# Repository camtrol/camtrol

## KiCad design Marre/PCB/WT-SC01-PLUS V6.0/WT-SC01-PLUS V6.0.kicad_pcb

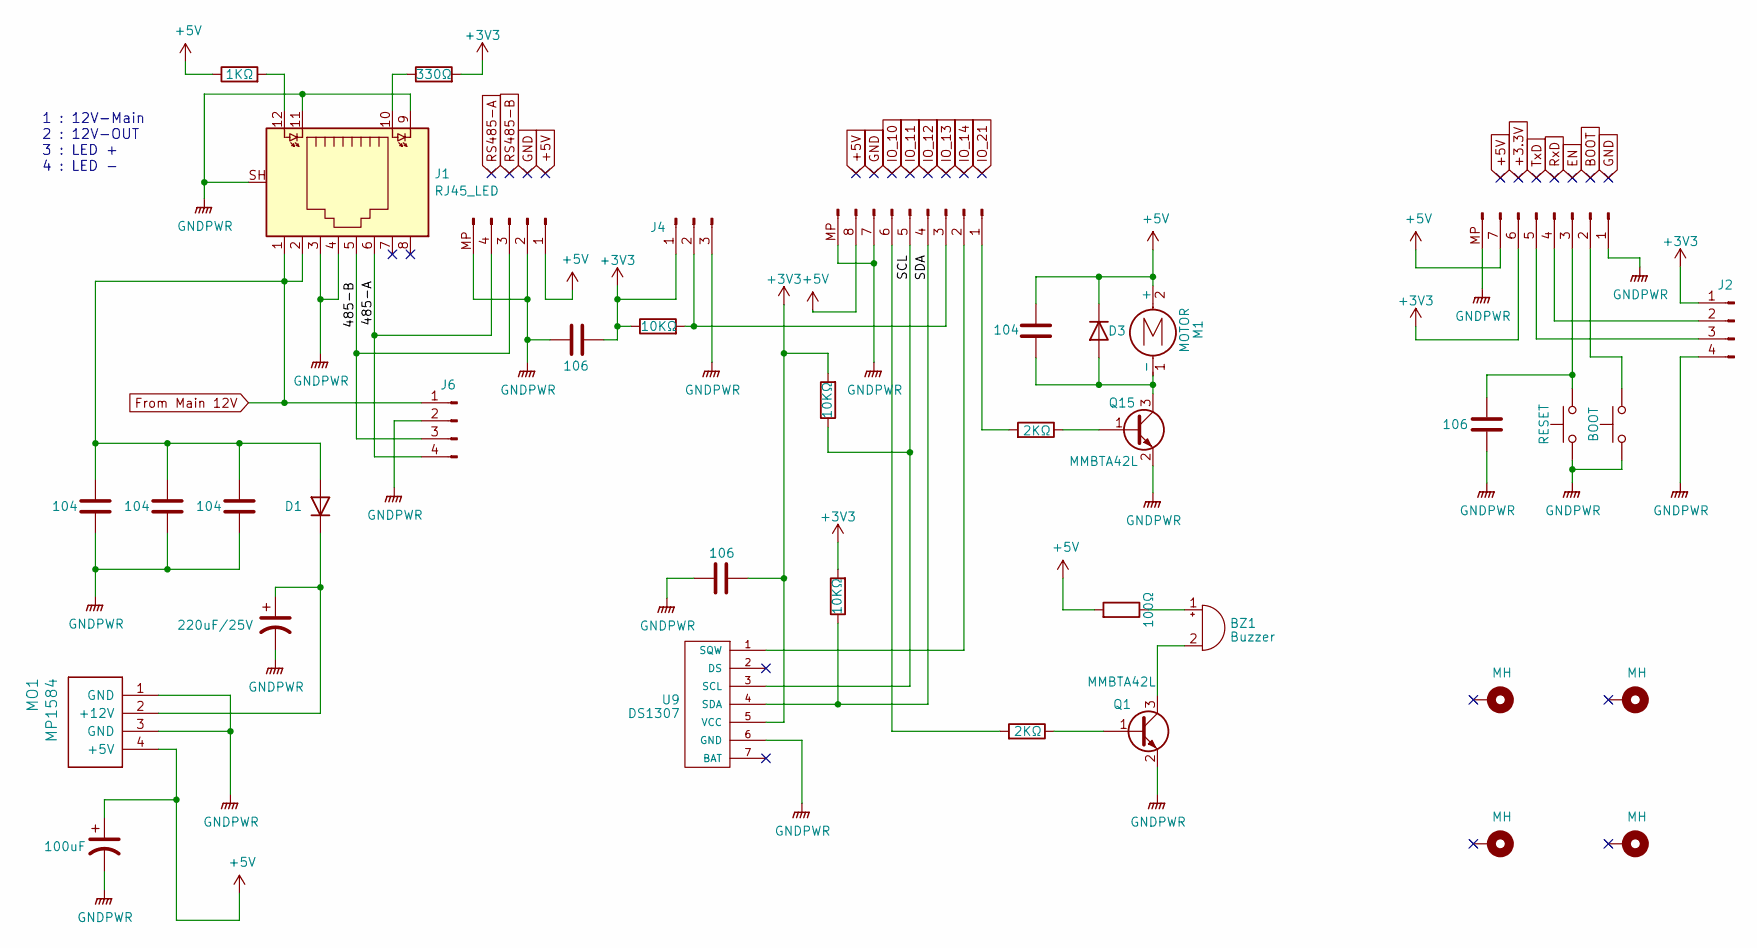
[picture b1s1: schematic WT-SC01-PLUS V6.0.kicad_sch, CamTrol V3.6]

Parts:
BZ1: Buzzer; Buzzer_12x9.5RM7.6
C1, C2, C5: 106; C_0805_HandSoldering
C3, C4, C15, C16: 104; C_0805_HandSoldering
C17: 100uF; CP_Elec_6.3x5.3
C22: 220uF/25V; CP_Radial_D8.0mm_P3.50mm
D1, D3: SS34; D_SMA
H3, H4, H5, H6: MH; MountingHole_SC01
J1: RJ45_LED; RJ45_LED_SMD
J2: 5267-04P; Molex_SPOX_5267-04A_1x04_P2.50mm_Vertical
J3: Conn_01x04_Pin; JST_GH_SM04B-GHS-TB_1x04-1MP_P1.25mm_Horizontal
J4: Conn_01x03_Pin; PhoenixContact_MCV_1,5_3-G-3.81_1x03_P3.81mm_Vertical
J5: Conn_01x08_Pin; JST_GH_SM08B-GHS-TB_1x08-1MP_P1.25mm_Horizontal
J6: 5267-04P; XH2.54-4P
J7: Conn_01x8_Male; JST_GH_SM07B-GHS-TB_1x07-1MP_P1.25mm_Horizontal
M1: MOTOR; 3610-Motor
MO1: MP1584; TZT-SMD
Q1, Q15: MMBTA42L; SOT-23
R1, R42, R43: 10KΩ; R_0805_HandSoldering
R2, R17: 2KΩ; R_0805_HandSoldering
R3: 100Ω; R_0805_HandSoldering
R4: 330Ω; R_0805_HandSoldering
R40: 1KΩ; R_0805_HandSoldering
SW1: BOOT; TS-3404
SW2: RESET; TS-3404
U9: DS1307

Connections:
+3V3: C1.1, C2.2, J2.1, J4.1, J7.6, R1.1, R4.2, R42.2, R43.2, U9.5 (VCC)
+5V: C3.1, C17.1, D3.2 (K), J3.1, J5.8, J7.7, M1.2 (+), MO1.4 (+5V), R3.2, R40.1
/485-A: J1.6, J3.4, J6.4
/485-B: J1.5, J3.3, J6.3
/SCL: J5.5, R42.1, U9.3 (SCL)
/SDA: J5.4, R43.1, U9.4 (SDA)
From Main 12V: C4.2, C15.2, C16.2, D1.1 (A), J1.1, J1.2, J6.1
GNDPWR: C1.2, C2.1, C4.1, C5.1, C15.1, C16.1, C17.2, C22.2, J1.3, J1.4, J1.9, J1.11, J1.SH, J2.4, J3.2, J3.MP (Pin_5), J4.3, J5.7, J5.MP (Pin_9), J6.2, J7.1, J7.MP (Pin_8), MO1.1 (GND), MO1.3 (GND), Q1.2 (E), Q15.2 (E), SW1.1, SW2.1, U9.6 (GND)
unnamed: BZ1.2 (+), Q1.3 (C)
unnamed: BZ1.1 (-), R3.1
unnamed: C22.1, D1.2 (K), MO1.2 (+12V)
unnamed: C3.2, D3.1 (A), M1.1 (-), Q15.3 (C)
unnamed: J1.10, R4.1
unnamed: J1.12, R40.2
unnamed: J2.2, J7.4
unnamed: J2.3, J7.5
unnamed: J4.2, J5.3, R1.2
unnamed: J5.1, R17.2
unnamed: J5.2, U9.1 (SQW)
unnamed: J5.6, R2.2
unnamed: J7.2, SW1.2
unnamed: C5.2, J7.3, SW2.2
unnamed: Q1.1 (B), R2.1
unnamed: Q15.1 (B), R17.1

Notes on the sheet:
1 : 12V-Main 2 : 12V-OUT 3 : LED + 4 : LED -

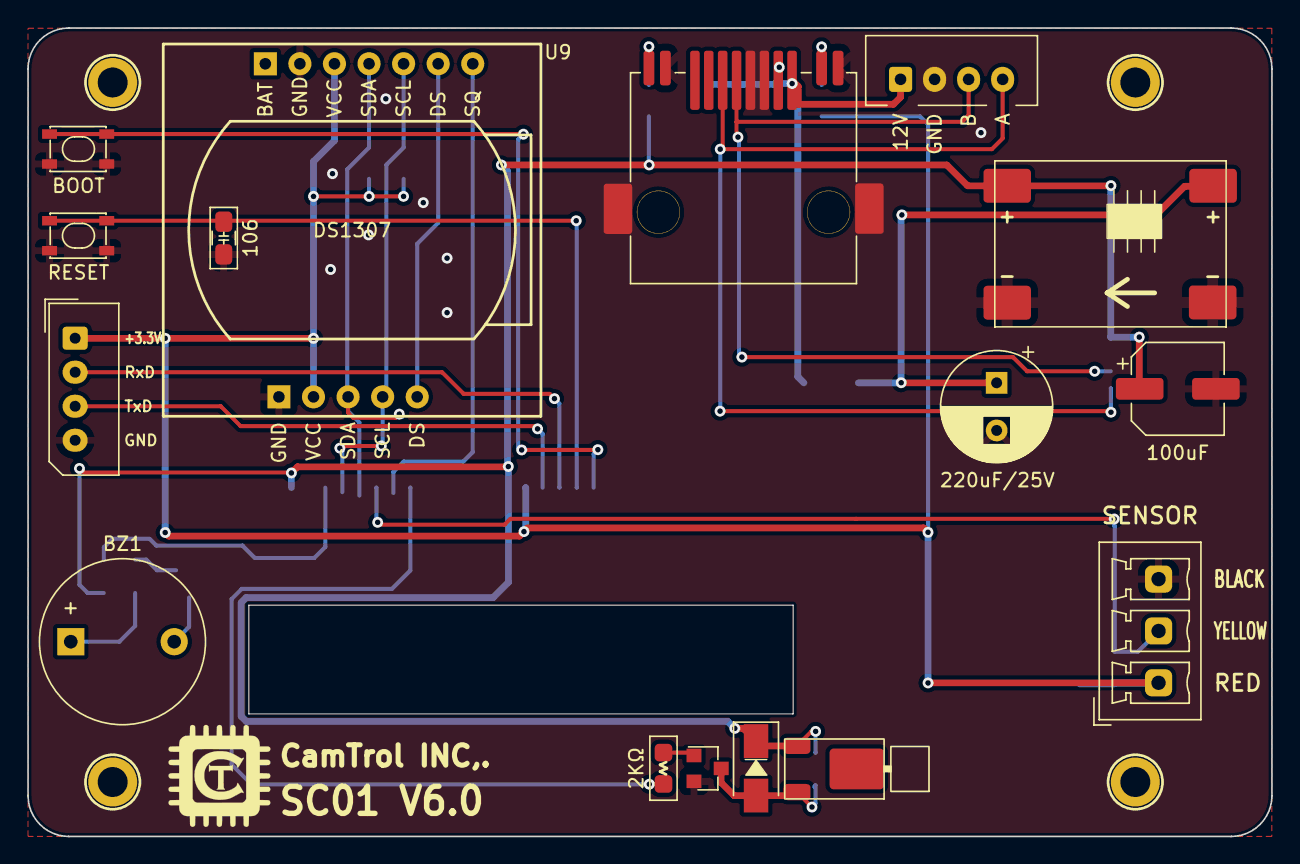
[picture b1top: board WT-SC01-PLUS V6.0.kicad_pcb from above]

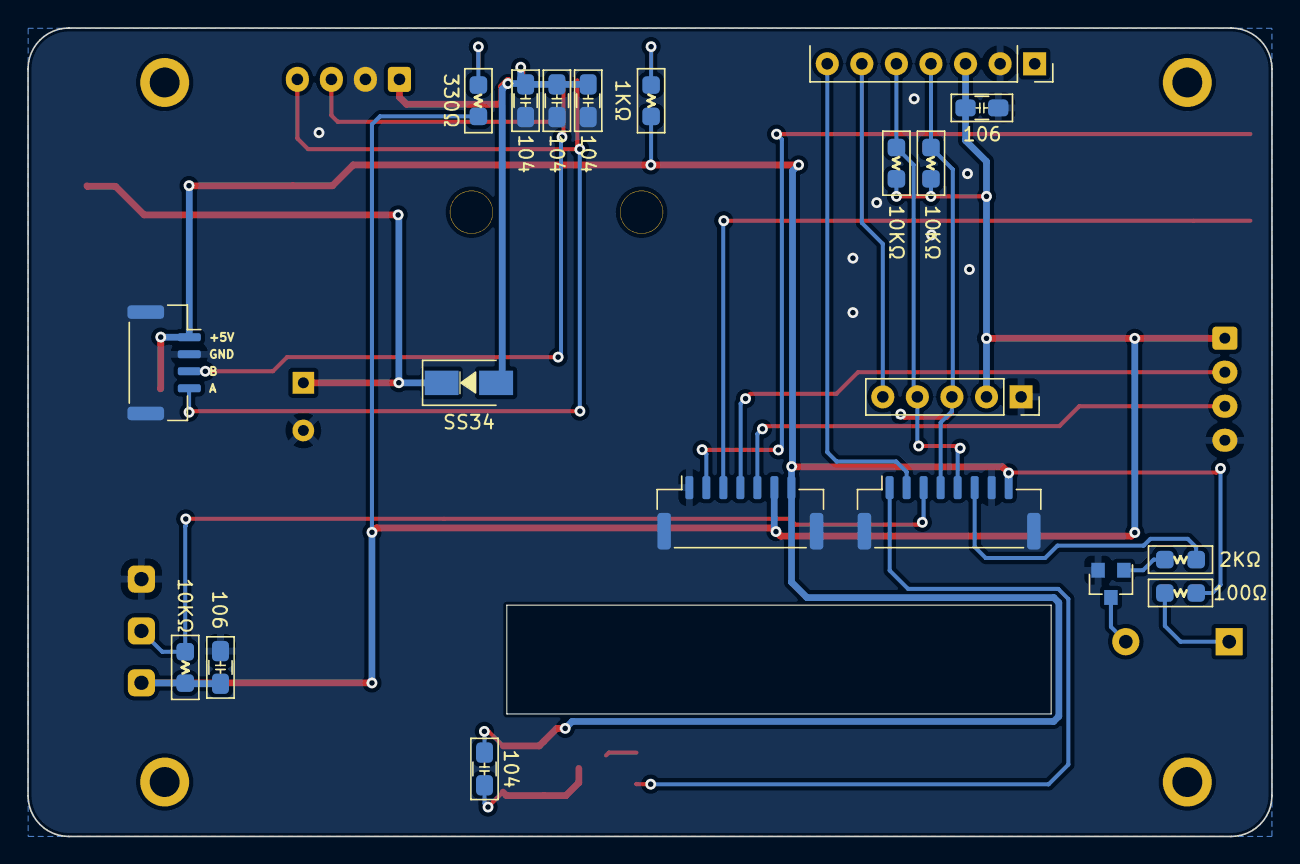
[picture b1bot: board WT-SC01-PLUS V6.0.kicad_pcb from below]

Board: 2 copper layers, 91.4 x 59.4 mm, 38 parts (18 on the bottom side), 24 nets.
